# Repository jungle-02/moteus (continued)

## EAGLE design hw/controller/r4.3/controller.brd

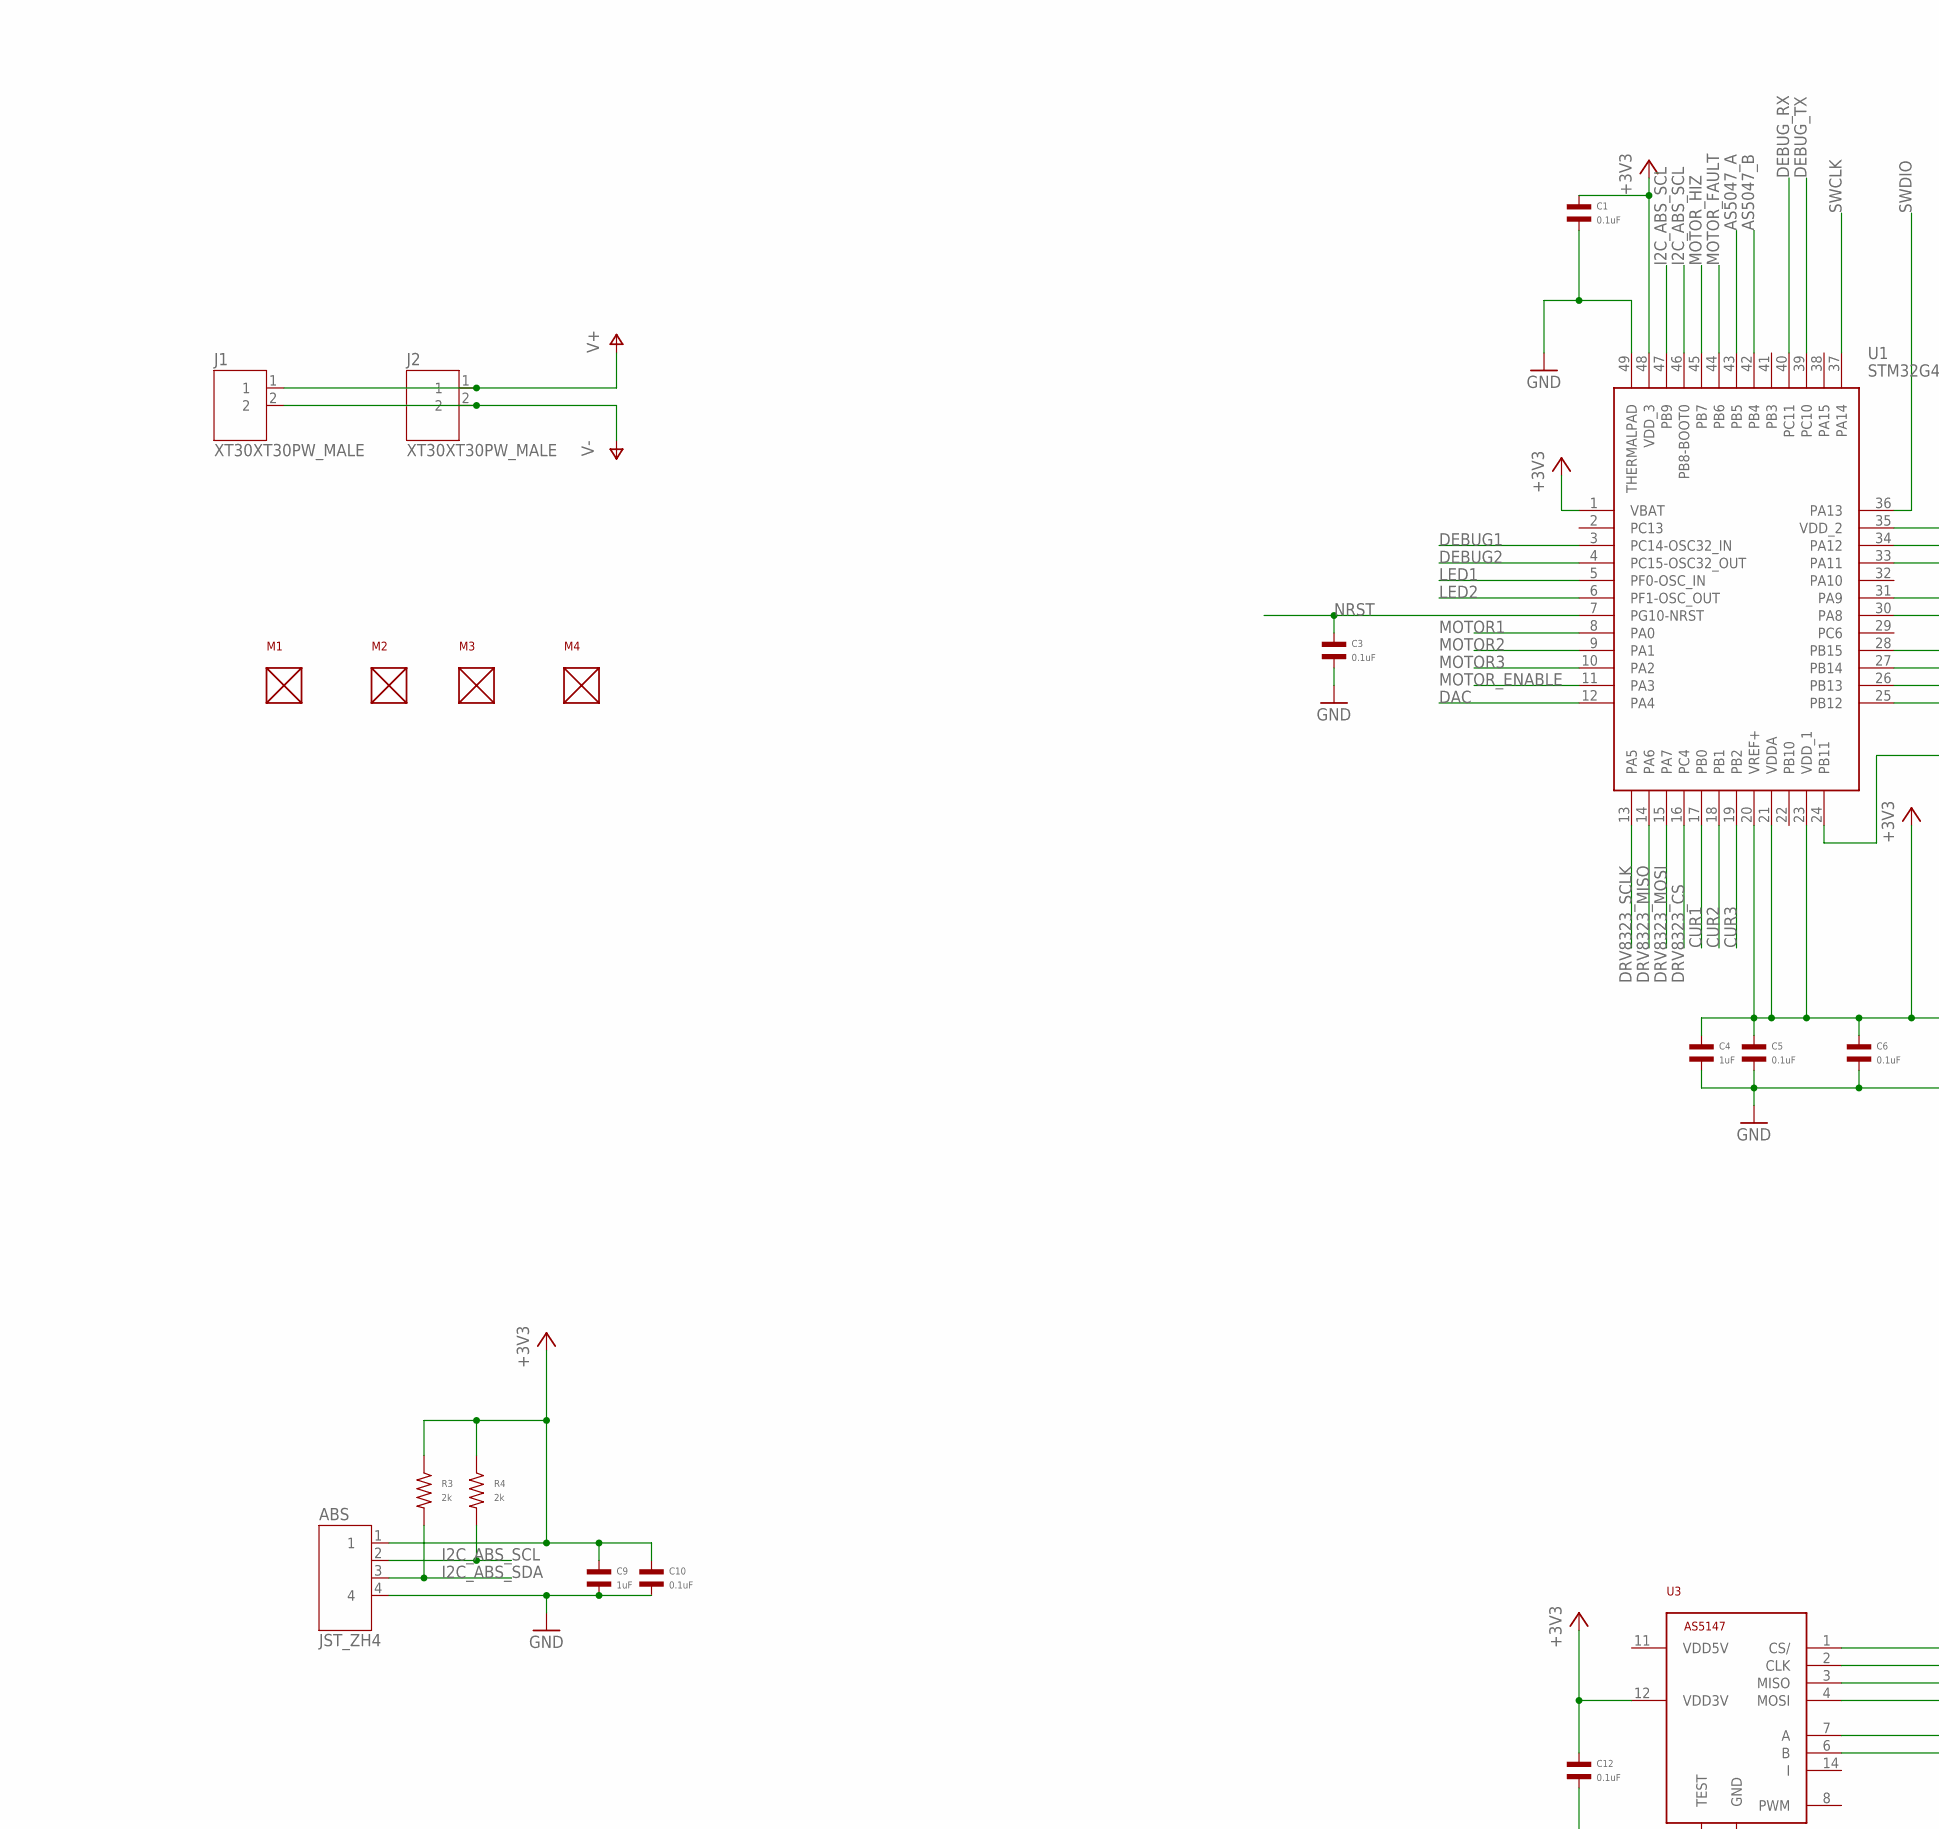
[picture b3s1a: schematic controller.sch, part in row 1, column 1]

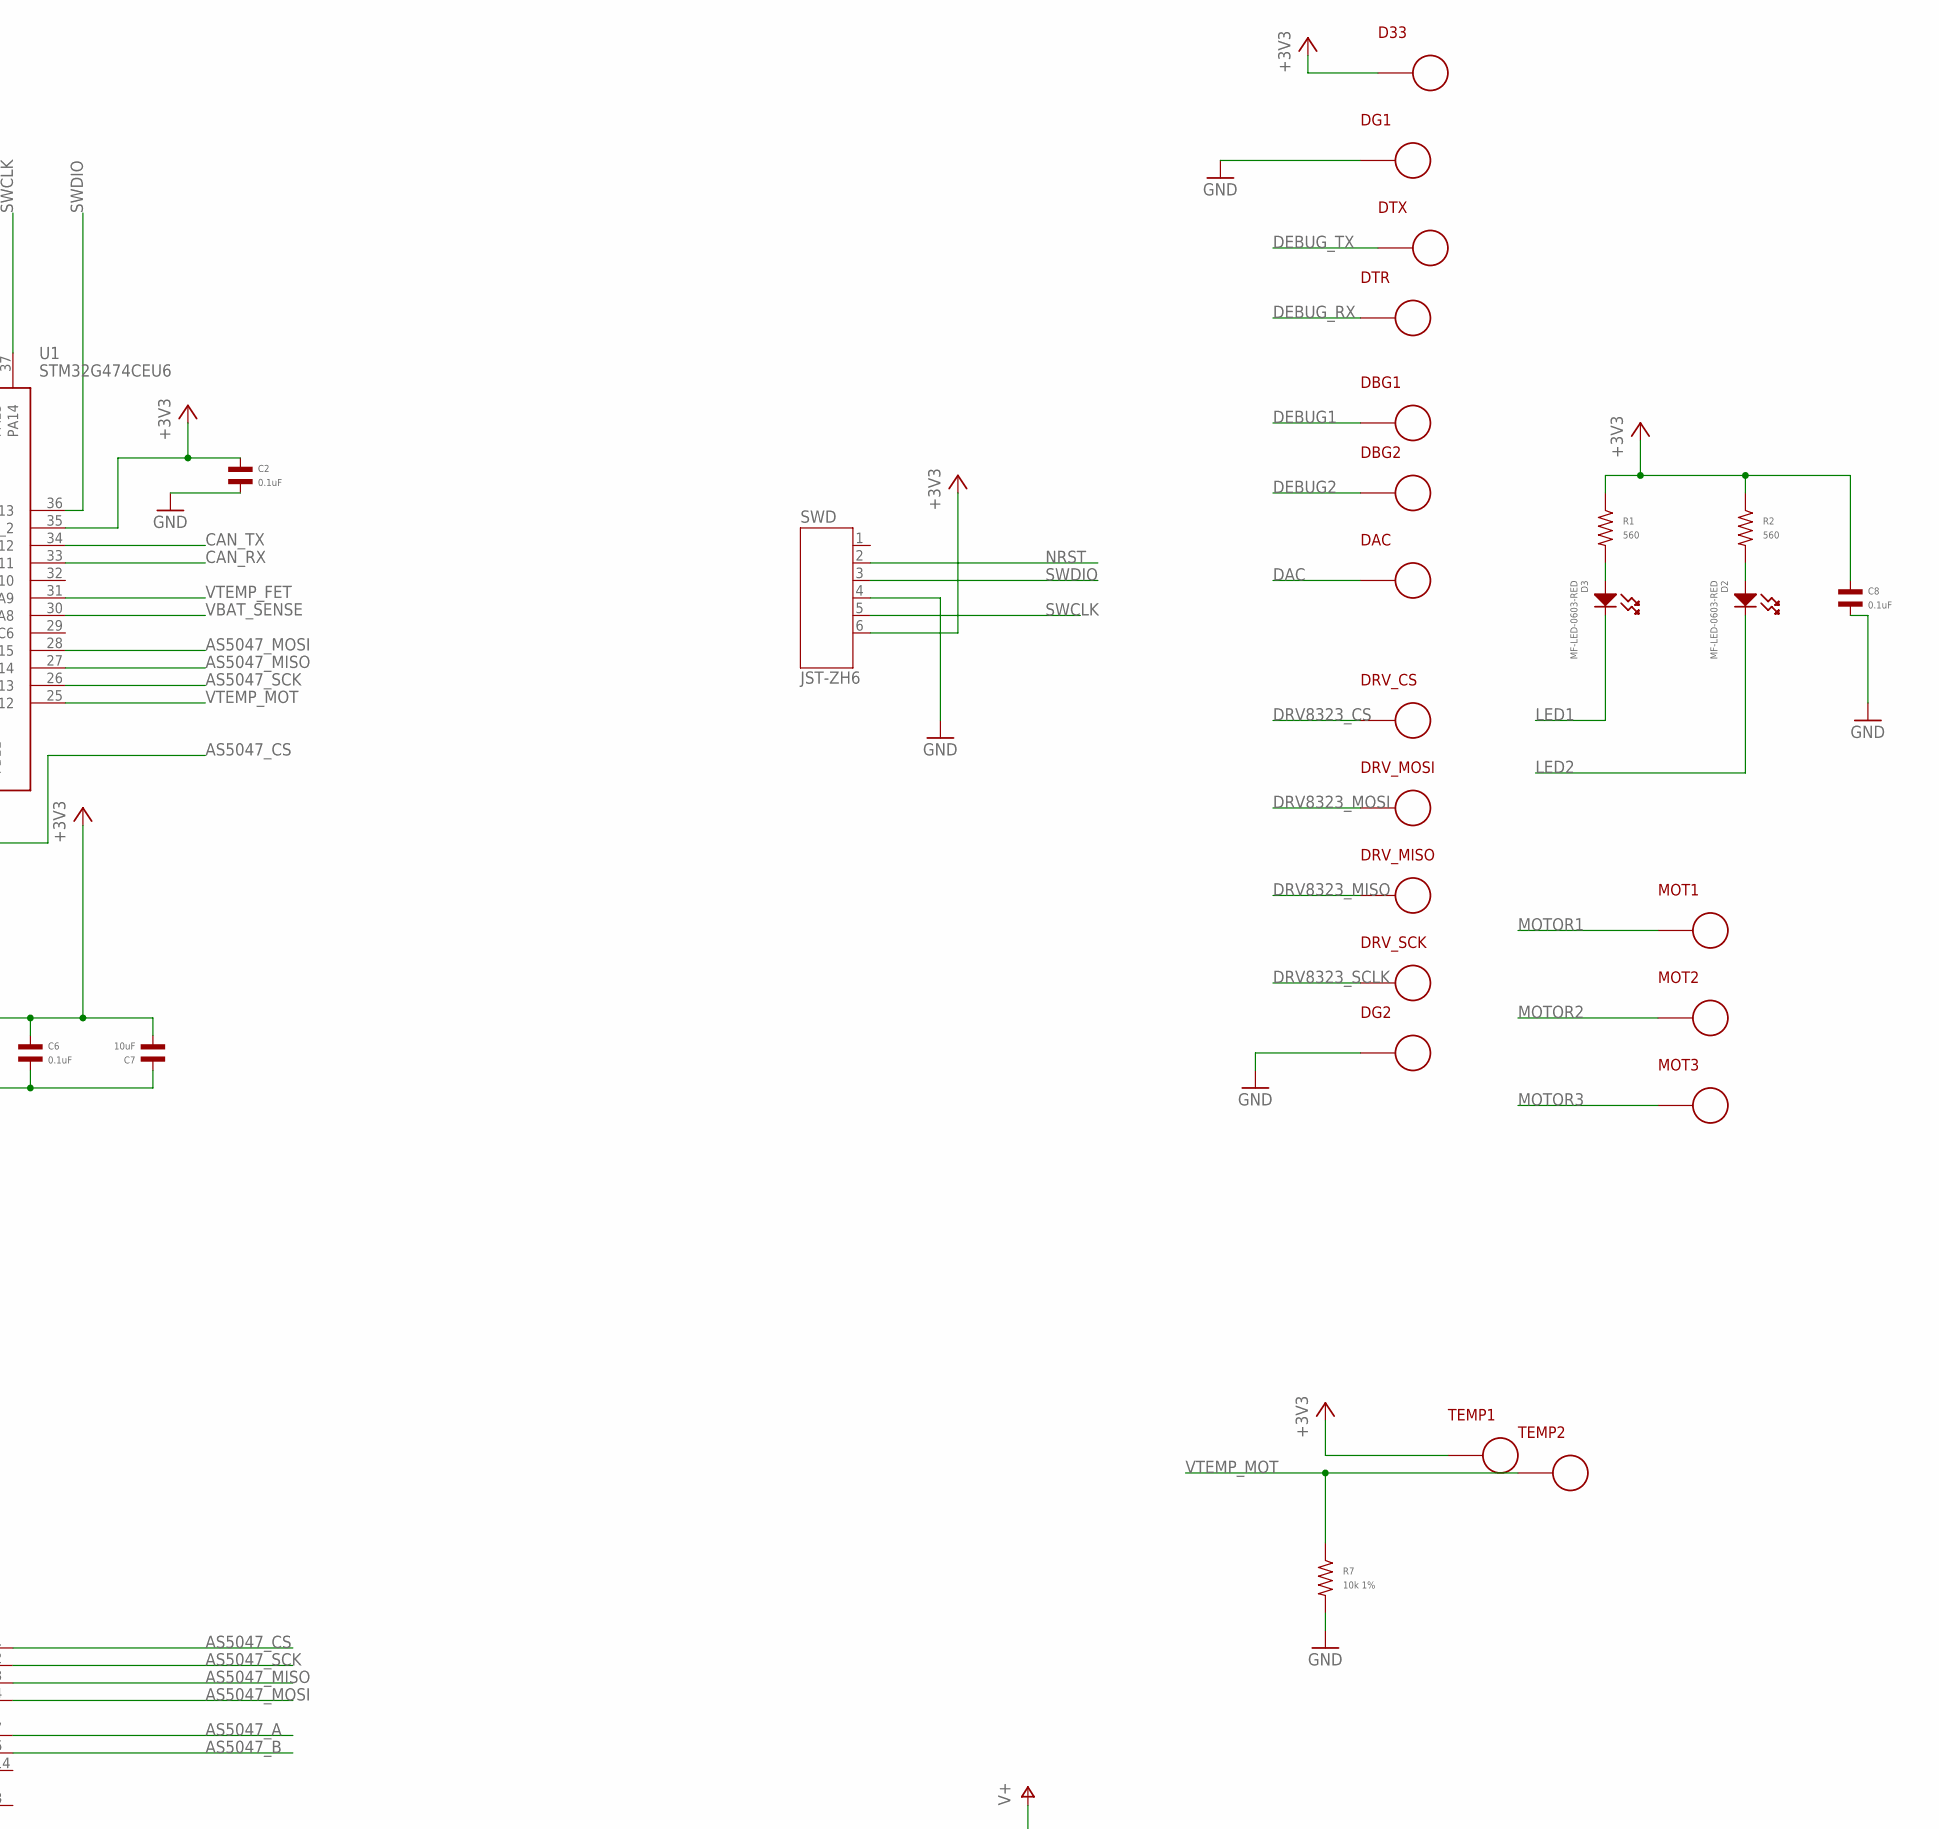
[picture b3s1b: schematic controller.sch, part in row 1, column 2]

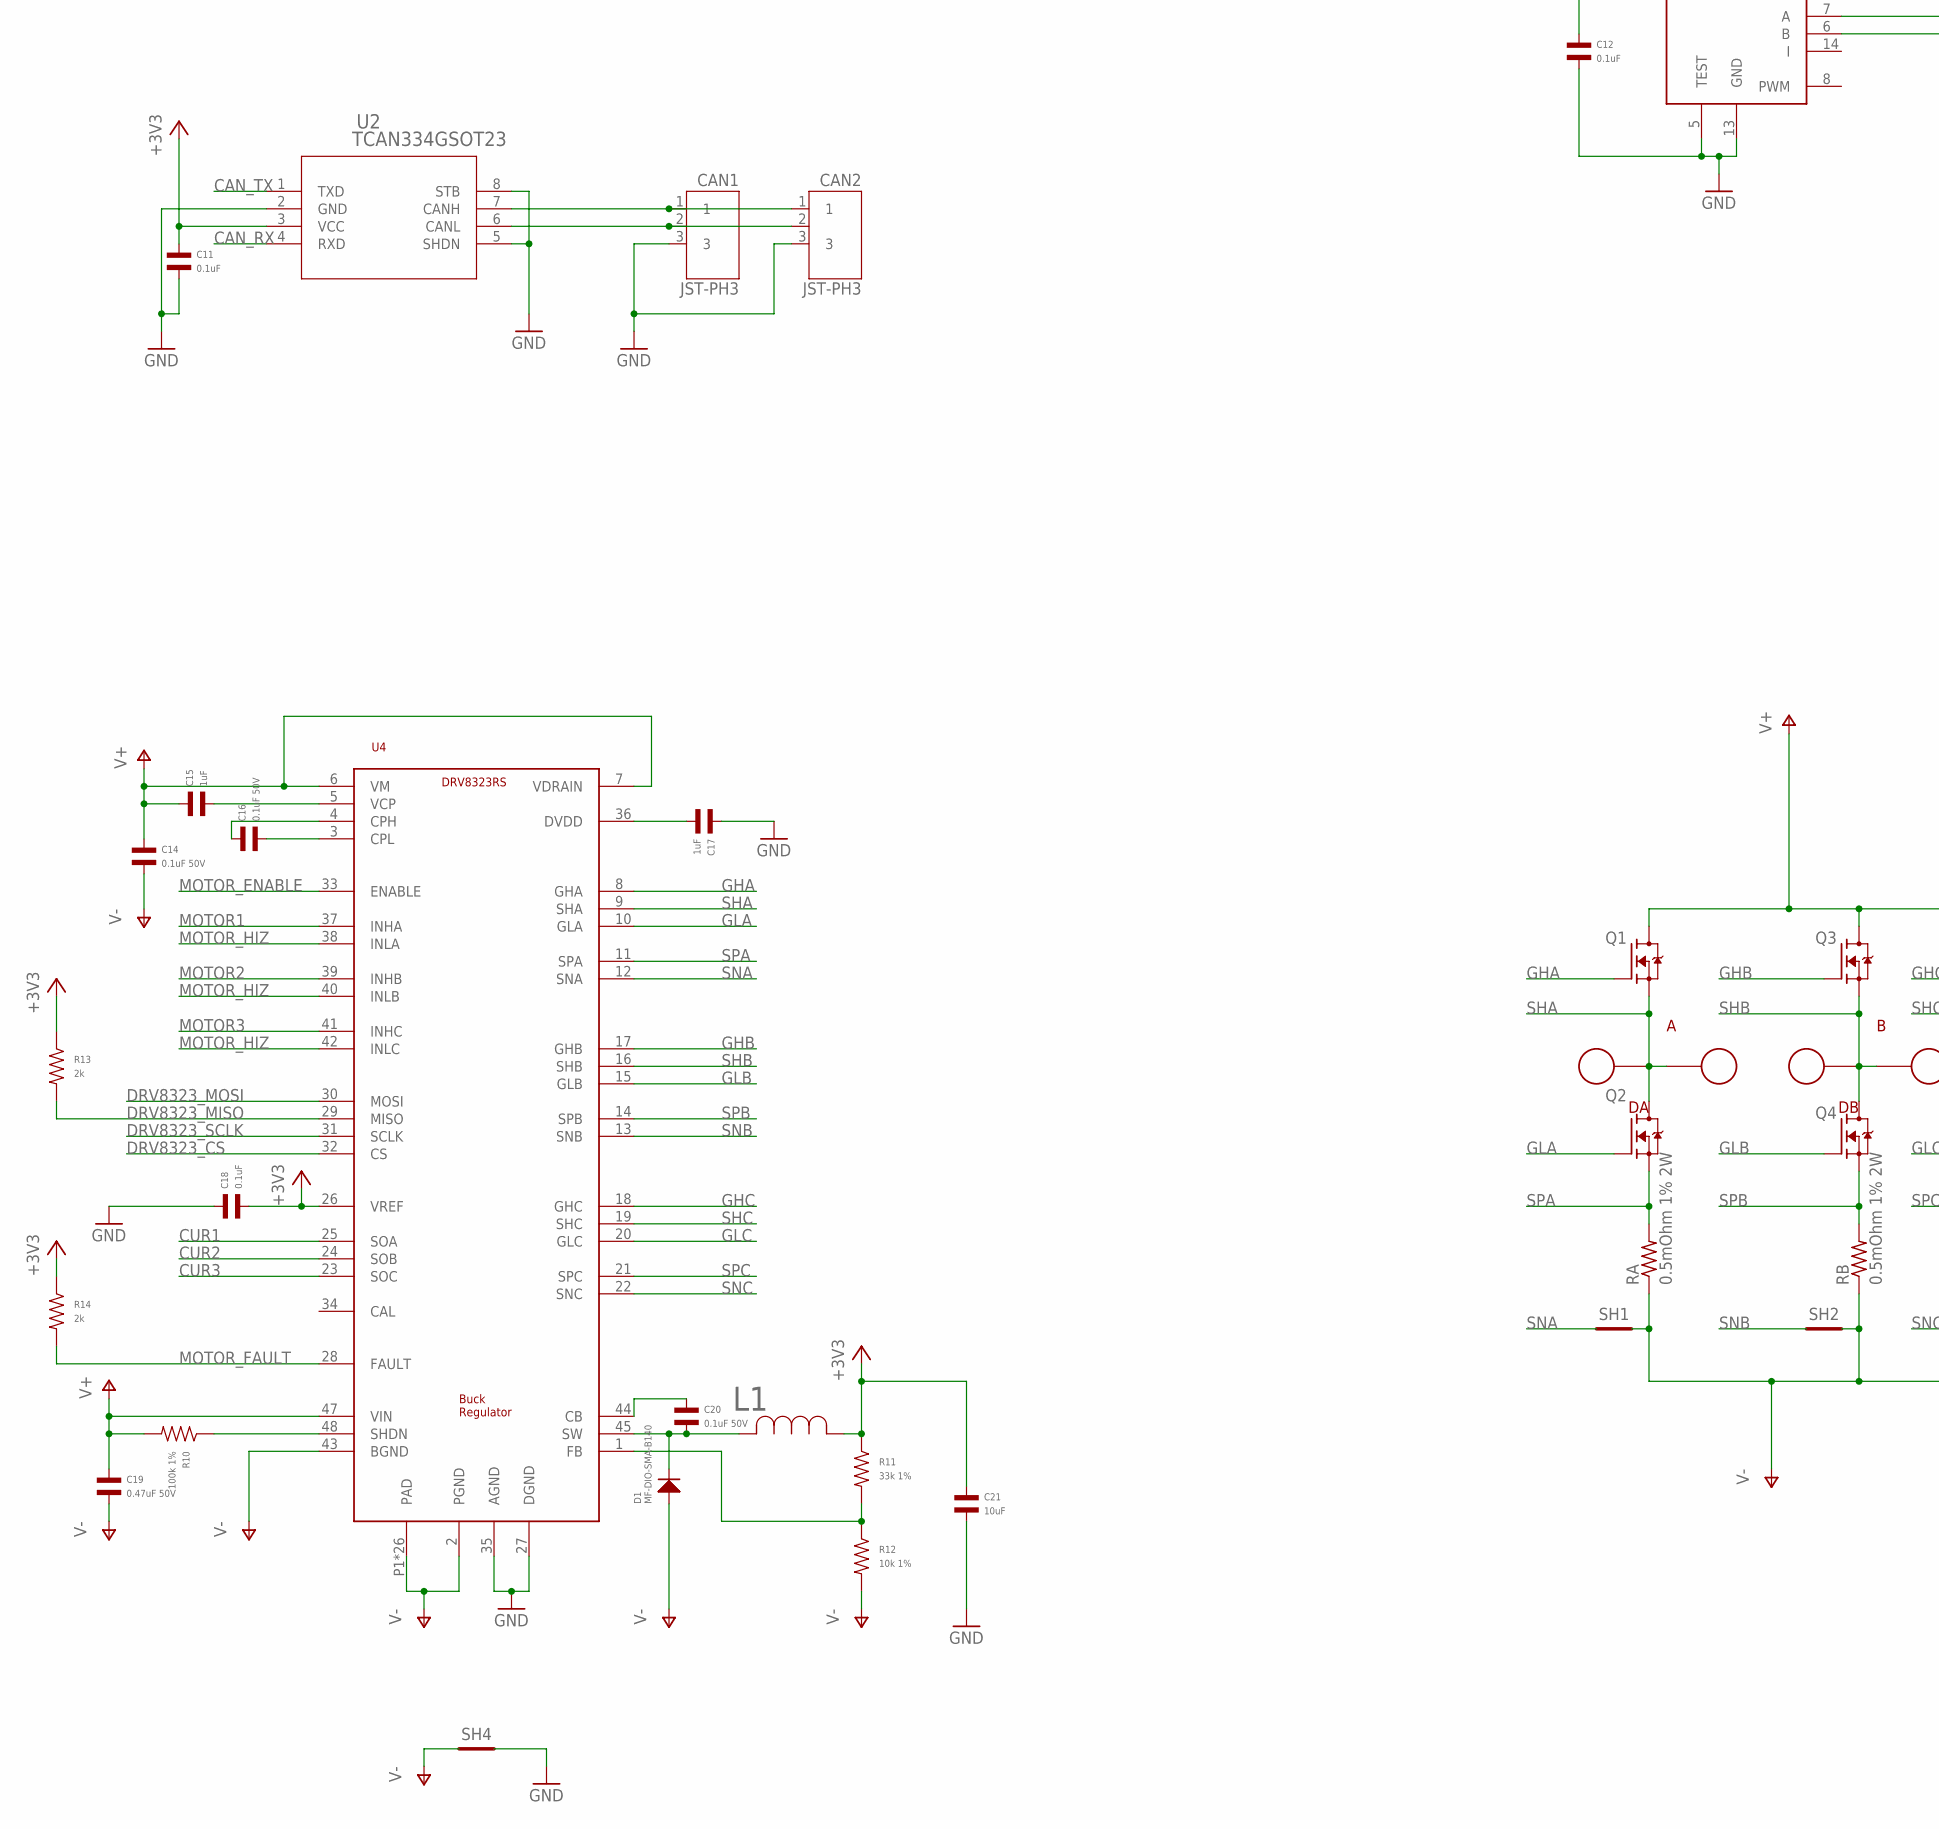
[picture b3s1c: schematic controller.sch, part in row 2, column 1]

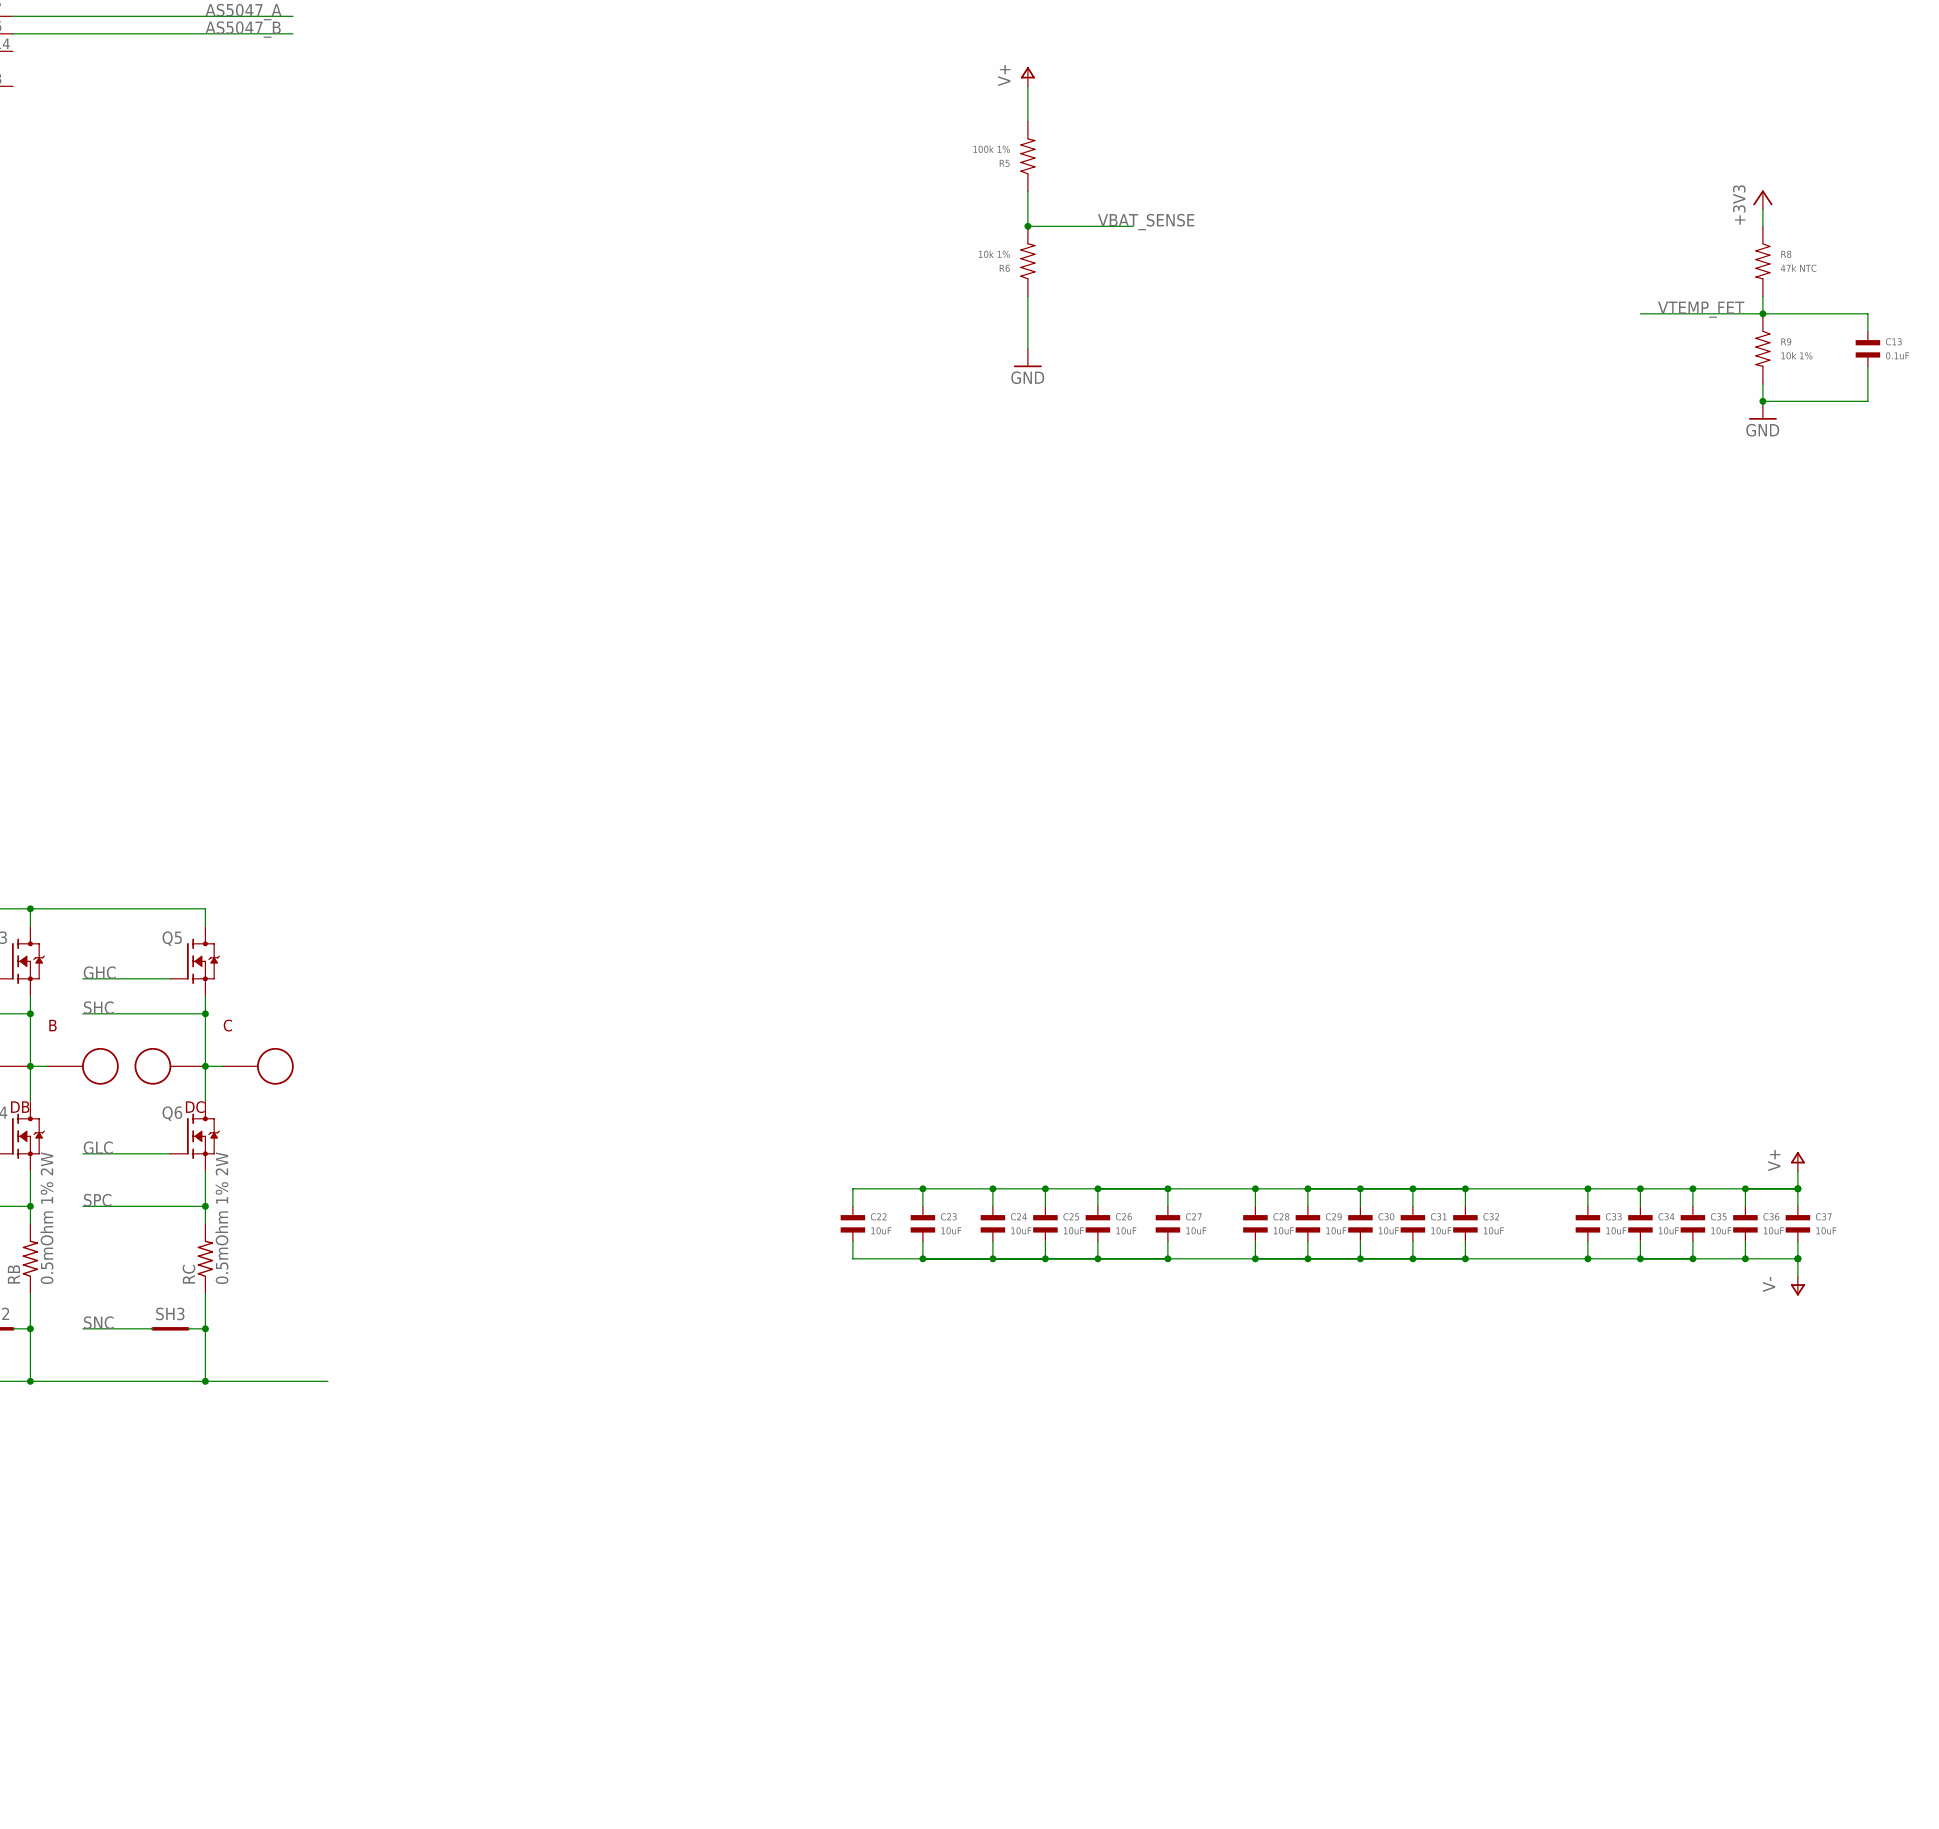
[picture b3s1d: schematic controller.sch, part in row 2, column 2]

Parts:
A: PAD; 18AWG_PAD
ABS: JST_ZH4; JST_S4B-ZR-SM4A-TF(LF)(SN); MPN S4B-ZR-SM4A-TF(LF)(SN)
B: PAD; 18AWG_PAD
C: PAD; 18AWG_PAD
C1, C2, C3, C5, C6, C8, C10, C11, C12, C13, C18: 0.1uF; C0402; MPN MF-CAP-0402-0.1uF
C4, C9, C15, C17: 1uF; C0402; MPN MF-CAP-0402-1uF
C7, C21: 10uF; C1206; MPN MF-CAP-1206-10uF
C14, C16, C20: 0.1uF 50V; C0402; MPN CGA2B3X7R1H104K050BB
C19: 0.47uF 50V; C0402; MPN UMK105ABJ474KV-F
C22, C23, C24, C25, C26, C27, C28, C29, C30, C31, C32, C33, C34, C35, C36, C37: 10uF; C1206; MPN CGA5L1X7R1H106K160AC
CAN1, CAN2: JST-PH3; JST_S3B-PH-SM4-TB(LF)(SN); MPN S3B-PH-SM4-TB(LF)(SN)
D1: MF-DIO-SMA-B140; SMA
D2: MF-LED-0603-RED; LED0603; MPN MF-LED-0603-GREEN
D3: MF-LED-0603-RED; LED0603
D33: PAD24AWG_PAD; 24AWG_PAD
DA: PAD24AWG_PAD; 24AWG_PAD
DAC: PAD24AWG_PAD; 24AWG_PAD
DB: PAD24AWG_PAD; 24AWG_PAD
DBG1, DBG2: PAD24AWG_PAD; 24AWG_PAD
DC: PAD24AWG_PAD; 24AWG_PAD
DG1, DG2: PAD24AWG_PAD; 24AWG_PAD
DRV_CS: PAD24AWG_PAD; 24AWG_PAD
DRV_MISO: PAD24AWG_PAD; 24AWG_PAD
DRV_MOSI: PAD24AWG_PAD; 24AWG_PAD
DRV_SCK: PAD24AWG_PAD; 24AWG_PAD
DTR: PAD24AWG_PAD; 24AWG_PAD
DTX: PAD24AWG_PAD; 24AWG_PAD
J1, J2: XT30XT30PW_MALE; XT30PW_MALE
L1: SRN4018-220M; IND_BOURNS_SRN4018; MPN SRN4018-220M
M1, M2, M3, M4: MOUNT; M2.5MOUNT
MOT1, MOT2, MOT3: PAD24AWG_PAD; 24AWG_PAD
Q1, Q2, Q3, Q4, Q5, Q6: TPH1R204PLSOP_ADVANCE_8; SOP_ADVANCE_8; MPN TPH1R204PL,L1Q
R1, R2: 560; R0402; MPN MF-RES-0402-560
R3, R4, R13, R14: 2k; R0402; MPN MF-RES-0402-2K
R5, R10: 100k 1%; R0402; MPN ERJ-2RKF1003X
R6, R7, R9, R12: 10k 1%; R0402; MPN ERJ-2RKF1002X
R8: 47k NTC; R0402; MPN NCP15WB473F03RC
R11: 33k 1%; R0402; MPN ERJ-2RKF3302X
RA: 0.5mOhm 1% 2W; M1206; MPN HCS1206FTL500
RB: 0.5mOhm 1% 2W; M1206; MPN HCS1206FTL500
RC: 0.5mOhm 1% 2W; M1206; MPN HCS1206FTL500
SH1, SH2, SH3: SHORTT5; SHORT_TOP-50
SH4: SHORTBIG; SHORT_TOP-BIG
SWD: JST-ZH6; JST_S6B-ZR-SM4A-TF(LF)(SN); MPN S6B-ZR-SM4A-TF(LF)(SN)
TEMP1, TEMP2: PAD24AWG_PAD; 24AWG_PAD
U1: STM32G474CEU6; QFN50P700X700X60-49N; MPN STM32G474CEU6
U2: TCAN334GSOT23; SOT23-8; MPN TCAN334GDCNT
U3: AS5147; TSSOP14; MPN AS5047P-ATSM
U4: DRV8323RS; PVQFN-N48; MPN DRV8323RSRGZR

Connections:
+3V3: ABS.1, C1.P$1, C2.P$1, C4.P$1, C5.P$1, C6.P$1, C7.P$2, C8.P$1, C9.P$1, C10.P$1, C11.P$1, C12.P$1, C18.P$2, C21.P$1, D33.P$1, L1.1, R1.P$1, R2.P$1, R3.P$1, R4.P$1, R8.P$1, R11.P$1, R13.P$1, R14.P$1, SWD.6, TEMP1.P$1, U1.1 (VBAT), U1.20 (VREF+), U1.21 (VDDA), U1.23 (VDD_1), U1.35 (VDD_2), U1.48 (VDD_3), U2.3 (VCC), U3.12 (VDD3V), U4.26 (VREF)
AS5047_A: U1.43 (PB5), U3.7 (A)
AS5047_B: U1.42 (PB4), U3.6 (B)
AS5047_CS: U1.24 (PB11), U3.1 (CS/)
AS5047_MISO: U1.27 (PB14), U3.3 (MISO)
AS5047_MOSI: U1.28 (PB15), U3.4 (MOSI)
AS5047_SCK: U1.26 (PB13), U3.2 (CLK)
CAN_N: CAN1.2, CAN2.2, U2.6 (CANL)
CAN_P: CAN1.1, CAN2.1, U2.7 (CANH)
CAN_RX: U1.33 (PA11), U2.4 (RXD)
CAN_TX: U1.34 (PA12), U2.1 (TXD)
CUR1: U1.17 (PB0), U4.25 (SOA)
CUR2: U1.18 (PB1), U4.24 (SOB)
CUR3: U1.19 (PB2), U4.23 (SOC)
DAC: DAC.P$1, U1.12 (PA4)
DEBUG1: DBG1.P$1, U1.3 (PC14-OSC32_IN)
DEBUG2: DBG2.P$1, U1.4 (PC15-OSC32_OUT)
DEBUG_RX: DTR.P$1, U1.40 (PC11)
DEBUG_TX: DTX.P$1, U1.39 (PC10)
DRV8323_CS: DRV_CS.P$1, U1.16 (PC4), U4.32 (CS)
DRV8323_MISO: DRV_MISO.P$1, R13.P$2, U1.14 (PA6), U4.29 (MISO)
DRV8323_MOSI: DRV_MOSI.P$1, U1.15 (PA7), U4.30 (MOSI)
DRV8323_SCLK: DRV_SCK.P$1, U1.13 (PA5), U4.31 (SCLK)
GHA: Q1.4 (G), U4.8 (GHA)
GHB: Q3.4 (G), U4.17 (GHB)
GHC: Q5.4 (G), U4.18 (GHC)
GLA: Q2.4 (G), U4.10 (GLA)
GLB: Q4.4 (G), U4.15 (GLB)
GLC: Q6.4 (G), U4.20 (GLC)
GND: ABS.4, C1.P$2, C2.P$2, C3.P$2, C4.P$2, C5.P$2, C6.P$2, C7.P$1, C8.P$2, C9.P$2, C10.P$2, C11.P$2, C12.P$2, C13.P$2, C17.P$1, C18.P$1, C21.P$2, CAN1.3, CAN2.3, DG1.P$1, DG2.P$1, R6.P$1, R7.P$2, R9.P$2, SH4.2, SWD.4, U1.49 (THERMALPAD), U2.2 (GND), U2.5 (SHDN), U2.8 (STB), U3.5 (TEST), U3.13 (GND), U4.27 (DGND), U4.35 (AGND)
I2C_ABS_SCL: ABS.2, R4.P$2, U1.46 (PB8-BOOT0), U1.47 (PB9)
I2C_ABS_SDA: ABS.3, R3.P$2
LED1: D3.CATHODE, U1.5 (PF0-OSC_IN)
LED2: D2.CATHODE, U1.6 (PF1-OSC_OUT)
MOTOR1: MOT1.P$1, U1.8 (PA0), U4.37 (INHA)
MOTOR2: MOT2.P$1, U1.9 (PA1), U4.39 (INHB)
MOTOR3: MOT3.P$1, U1.10 (PA2), U4.41 (INHC)
MOTOR_ENABLE: U1.11 (PA3), U4.33 (ENABLE)
MOTOR_FAULT: R14.P$2, U1.44 (PB6), U4.28 (FAULT)
MOTOR_HIZ: U1.45 (PB7), U4.38 (INLA), U4.40 (INLB), U4.42 (INLC)
unnamed: R10.P$1, U4.48 (SHDN)
unnamed: R11.P$2, R12.P$1, U4.1 (FB)
unnamed: C16.P$2, U4.3 (CPL)
unnamed: C20.P$2, D1.CATHODE, L1.2, U4.45 (SW)
unnamed: C20.P$1, U4.44 (CB)
unnamed: C16.P$1, U4.4 (CPH)
unnamed: C15.P$2, U4.5 (VCP)
unnamed: C17.P$2, U4.36 (DVDD)
unnamed: D3.ANODE, R1.P$2
unnamed: D2.ANODE, R2.P$2
NRST: C3.P$1, SWD.2, U1.7 (PG10-NRST)
SHA: A.1, DA.P$1, Q1.1 (S), Q1.2 (S), Q1.3 (S), Q2.5 (D), Q2.6 (D), Q2.7 (D), Q2.8 (D), Q2.PAD (D), U4.9 (SHA)
SHB: B.1, DB.P$1, Q3.1 (S), Q3.2 (S), Q3.3 (S), Q4.5 (D), Q4.6 (D), Q4.7 (D), Q4.8 (D), Q4.PAD (D), U4.16 (SHB)
SHC: C.1, DC.P$1, Q5.1 (S), Q5.2 (S), Q5.3 (S), Q6.5 (D), Q6.6 (D), Q6.7 (D), Q6.8 (D), Q6.PAD (D), U4.19 (SHC)
SNA: SH1.1, U4.12 (SNA)
SNB: SH2.1, U4.13 (SNB)
SNC: SH3.1, U4.22 (SNC)
SPA: Q2.1 (S), Q2.2 (S), Q2.3 (S), RA.2, U4.11 (SPA)
SPB: Q4.1 (S), Q4.2 (S), Q4.3 (S), RB.2, U4.14 (SPB)
SPC: Q6.1 (S), Q6.2 (S), Q6.3 (S), RC.2, U4.21 (SPC)
SWCLK: SWD.5, U1.37 (PA14)
SWDIO: SWD.3, U1.36 (PA13)
V+: C14.P$1, C15.P$1, C19.P$1, C22.P$1, C23.P$1, C24.P$1, C25.P$1, C26.P$1, C27.P$1, C28.P$1, C29.P$1, C30.P$1, C31.P$1, C32.P$1, C33.P$1, C34.P$1, C35.P$1, C36.P$1, C37.P$1, J1.1, J2.1, Q1.5 (D), Q1.6 (D), Q1.7 (D), Q1.8 (D), Q1.PAD (D), Q3.5 (D), Q3.6 (D), Q3.7 (D), Q3.8 (D), Q3.PAD (D), Q5.5 (D), Q5.6 (D), Q5.7 (D), Q5.8 (D), Q5.PAD (D), R5.P$2, R10.P$2, U4.6 (VM), U4.7 (VDRAIN), U4.47 (VIN)
V-: C14.P$2, C19.P$2, C22.P$2, C23.P$2, C24.P$2, C25.P$2, C26.P$2, C27.P$2, C28.P$2, C29.P$2, C30.P$2, C31.P$2, C32.P$2, C33.P$2, C34.P$2, C35.P$2, C36.P$2, C37.P$2, D1.ANODE, J1.2, J2.2, R12.P$2, RA.1, RB.1, RC.1, SH1.2, SH2.2, SH3.2, SH4.1, U4.2 (PGND), U4.43 (BGND), U4.P1 (PAD), U4.P2 (PAD), U4.P3 (PAD), U4.P4 (PAD), U4.P5 (PAD), U4.P6 (PAD), U4.P7 (PAD), U4.P8 (PAD), U4.P9 (PAD), U4.P10 (PAD), U4.P11 (PAD), U4.P12 (PAD), U4.P13 (PAD), U4.P14 (PAD), U4.P15 (PAD), U4.P16 (PAD), U4.P17 (PAD), U4.P18 (PAD), U4.P19 (PAD), U4.P20 (PAD), U4.P21 (PAD), U4.P22 (PAD), U4.P23 (PAD), U4.P24 (PAD), U4.P25 (PAD), U4.PAD
VBAT_SENSE: R5.P$1, R6.P$2, U1.30 (PA8)
VTEMP_FET: C13.P$1, R8.P$2, R9.P$1, U1.31 (PA9)
VTEMP_MOT: R7.P$1, TEMP2.P$1, U1.25 (PB12)

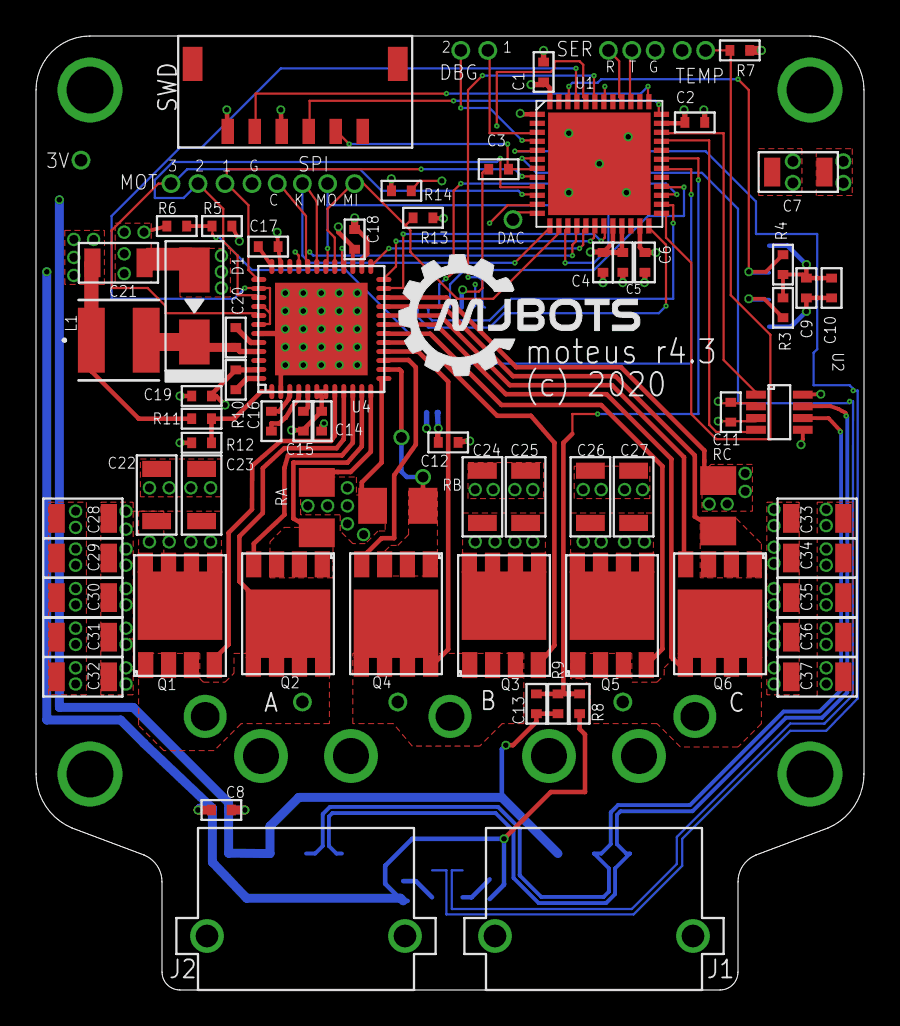
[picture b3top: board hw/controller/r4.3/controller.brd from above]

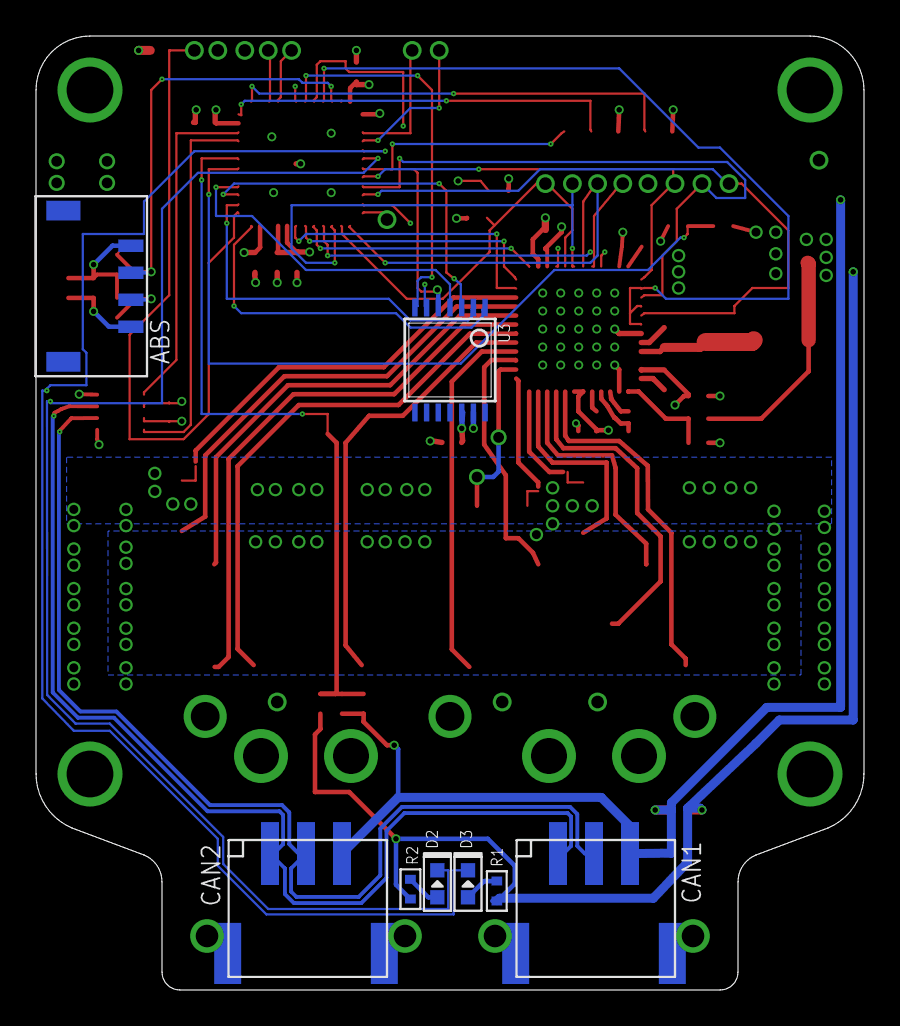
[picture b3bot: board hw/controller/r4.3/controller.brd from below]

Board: 4 copper layers, 46.0 x 53.0 mm, 105 parts (8 on the bottom side), 67 nets.

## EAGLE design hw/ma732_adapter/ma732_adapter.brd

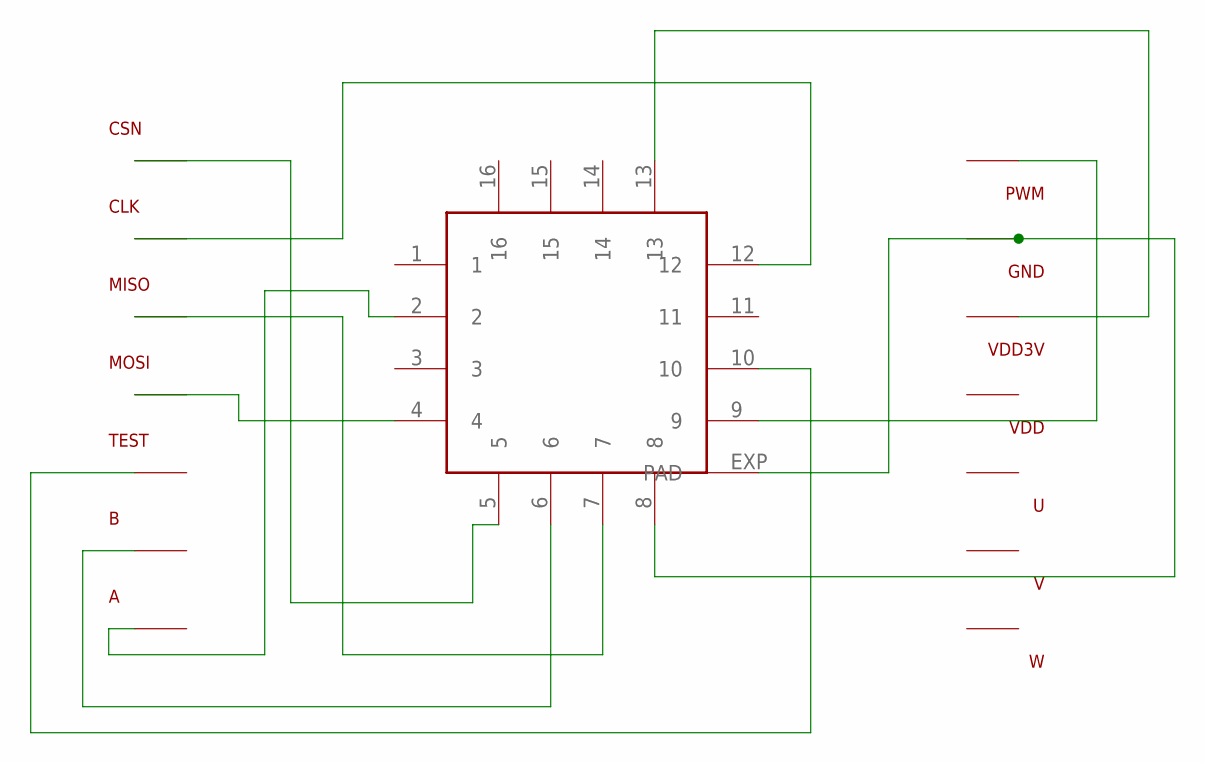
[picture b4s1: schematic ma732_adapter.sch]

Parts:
A: TSSOP_PAD
B: TSSOP_PAD
CLK: TSSOP_PAD
CSN: TSSOP_PAD
GND: TSSOP_PAD
MISO: TSSOP_PAD
MOSI: TSSOP_PAD
PWM: TSSOP_PAD
TEST: TSSOP_PAD
U: TSSOP_PAD
U$1: QFN16-BO; QFN16
V: TSSOP_PAD
VDD, VDD3V: TSSOP_PAD
W: TSSOP_PAD

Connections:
unnamed: CSN.P$1, U$1.5
unnamed: CLK.P$1, U$1.12
unnamed: MISO.P$1, U$1.7
unnamed: MOSI.P$1, U$1.4
unnamed: TEST.P$1, U$1.10
unnamed: B.P$1, U$1.6
unnamed: A.P$1, U$1.2
unnamed: PWM.P$1, U$1.9
unnamed: GND.P$1, U$1.8, U$1.EXP (PAD)
unnamed: U$1.13, VDD3V.P$1

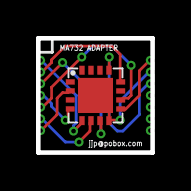
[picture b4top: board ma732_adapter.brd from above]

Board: 2 copper layers, 6.3 x 6.3 mm, 15 parts (0 on the bottom side), 10 nets.

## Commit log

2025-11-09 Fix another typo in the new docs
2025-11-09 Cau hinh Bazel tao compile_commands
2025-11-10 Ignore Bazel build outputs and external dependencies
2026-04-17 add fw_estimate
2026-04-29 Initial plan
2026-04-29 Add fw/mpc_kalman_estimator.h: MPC + Kalman Filter estimator for BLDC motor control
    Agent-Logs-Url: https://github.com/jungle-02/moteus/sessions/e9e625f3-5912-45d7-819a-79ee3ac8f89e
2026-04-29 Fix review findings: p_f cast, step trajectory angle, Inv22 epsilon guard, Cholesky comment
    Agent-Logs-Url: https://github.com/jungle-02/moteus/sessions/e9e625f3-5912-45d7-819a-79ee3ac8f89e
2026-04-29 Improve Mineq_ comment clarity (upper/lower constraint block labels)
    Agent-Logs-Url: https://github.com/jungle-02/moteus/sessions/e9e625f3-5912-45d7-819a-79ee3ac8f89e
2026-05-05 add fw_smo2
2026-05-05 Add comprehensive system flowchart for MPC+Kalman+SMO+RLS integration
2026-05-28 Document real SVPWM firmware execution sequence
